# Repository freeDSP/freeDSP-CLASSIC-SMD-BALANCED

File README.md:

# freeDSP-CLASSIC-SMD-BALANCED 
SMD Version with 1 I2S expansion header and balanced inputs/outputs and freeUSBi onboard.

## Upgrades from CLASSIC SMD A
- balanced audio inputs and outputs
- supports balanced interconnections with +6dBu (ARD nominal signal level)
- supports unbalanced interconnections with -10dBV (consumer audio nominal signal level)
- OpAmps supplied with +5V
- DC power input on barrel jack
- 1 standard I2S expansion header

For more information, please refer to the website [freedsp.github.io](https://freedsp.github.io/) and the documentation.  

## Status
Ready

## License

This work and all other materials under https://github.com/freeDSP are licensed under a <a rel="license" href="http://creativecommons.org/licenses/by-sa/4.0/legalcode">Creative Commons Attribution Share-Alike 4.0 license</a>. This allows for both personal and commercial derivative works, as long as they credit freeDSP and release their designs under the same license.

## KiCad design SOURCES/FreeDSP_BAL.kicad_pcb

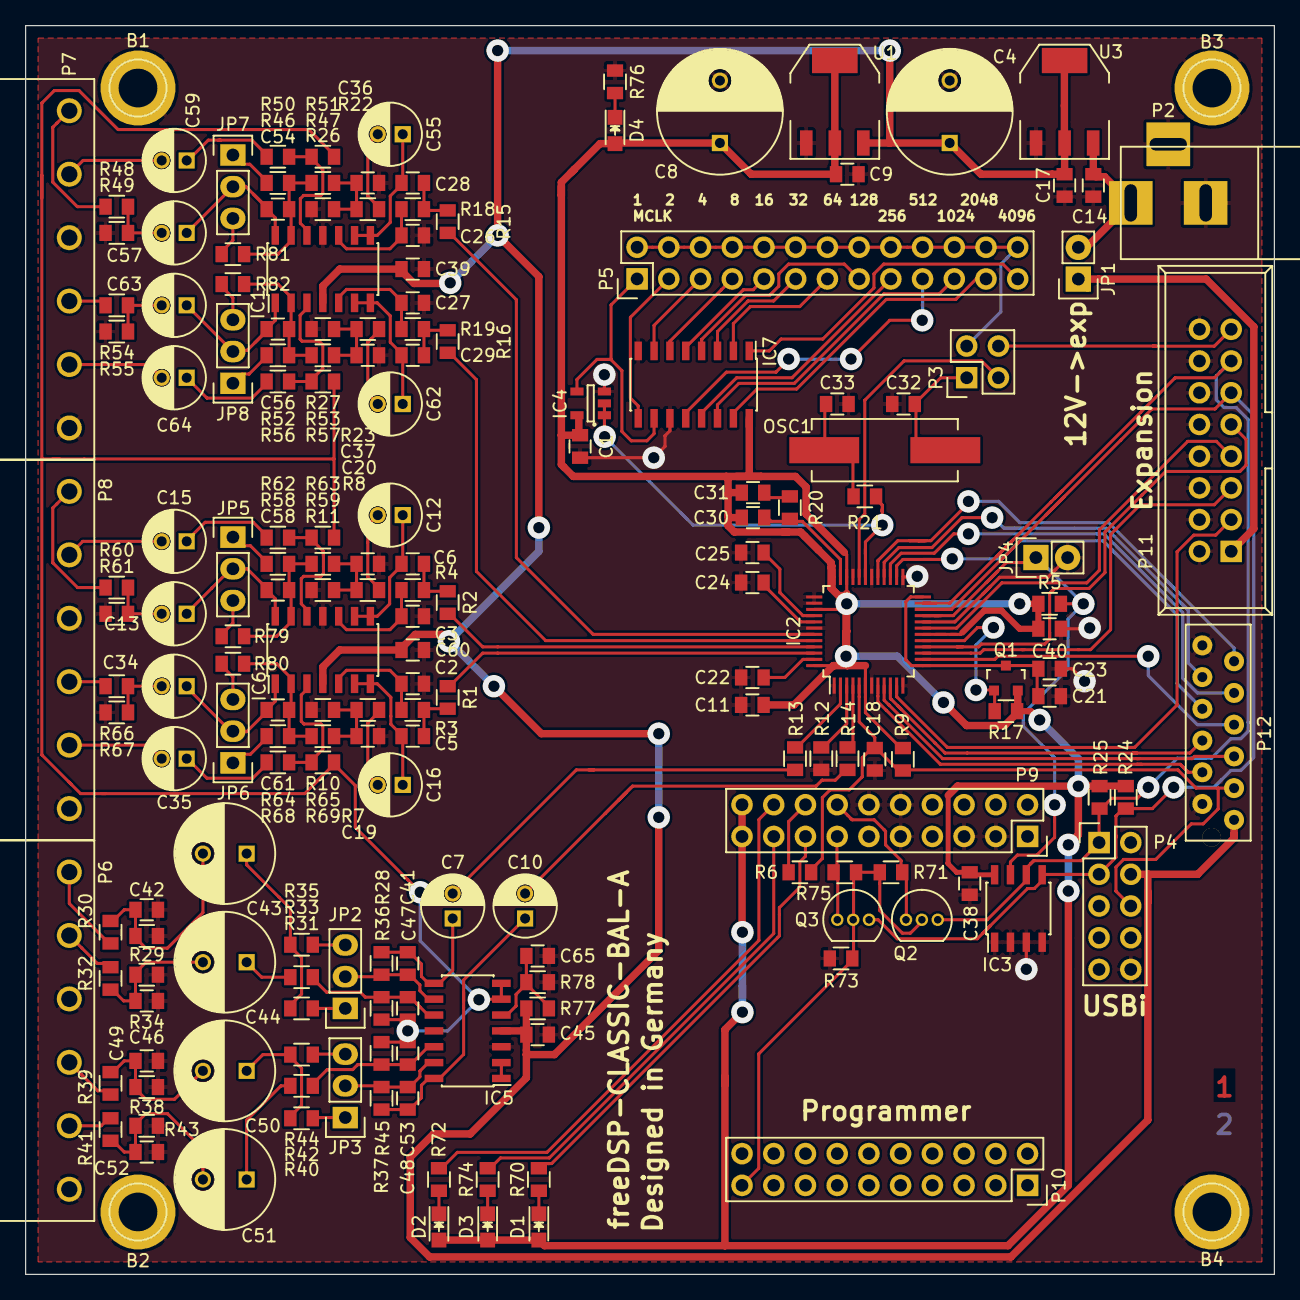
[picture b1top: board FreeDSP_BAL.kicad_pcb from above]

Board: 2 copper layers, 100.0 x 100.0 mm, 187 parts (0 on the bottom side), 148 nets.

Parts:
B1, B2, B3, B4: TEST_1P; 1pin
C1, C17, C23, C38, C39, C40, C45, C60, C65: 100n; C0805-X7R
C2, C3, C26, C27: 150p; C0805-X7R
C4, C8: 220u./35V; C_Radial_D10_L13_P5
C5, C6, C28, C29: 470p; C0805-X7R
C7, C10, C12, C13, C15, C16, C34, C35, C55, C57, C59, C62, C63, C64: 47u0./16V; C_Radial_D5_L11_P2
C9, C11, C14, C21, C22, C24, C25: 10u0; C0805-X7R
C18: 10n0; C0805-X7R
C19, C20, C30, C36, C37: 3n30; C0805-X7R
C31: 56n0; C0805-X7R
C32, C33: 22p0; C0805-X7R
C41, C47, C48, C53: 27p0; C0805-X7R
C42, C46, C49, C52: 100p; C0805-X7R
C43, C44, C50, C51: 47u0./35V; C_Radial_D8_L11.5_P3.5
C54, C56, C58, C61: 47p0; C0805-X7R
D1, D4: GREEN; LED_0805
D2, D3: RED; LED_0805
IC1, IC5, IC6: AD8608ARZ; SOIC-14_3.9x8.7mm_Pitch1.27mm
IC2: ADAU1701; LQFP-48_7x7mm_Pitch0.5mm
IC3: 24AA256; SOIC-8_3.9x4.9mm_Pitch1.27mm
IC4: SN74LVC1G08DBVR; SOT-23-5
IC7: 74HC4040D; SOIC-16_3.9x9.9mm_Pitch1.27mm
JP1, JP4: JUMPER; Pin_Header_Straight_1x02
JP2, JP3, JP5, JP6, JP7, JP8: JUMPER3; Pin_Header_Straight_1x03
OSC1: 24M576Hz; Crystal_HC49-SD_SMD
P2: BARREL_JACK
P3: CONN_02X02; Pin_Header_Straight_2x02
P4: USBi; Pin_Header_Straight_2x05
P5: CONN_02X13; Pin_Header_Straight_2x13
P6, P7, P8: CONN_01X06; SL_5.08HC-06-90
P9, P10: CONN_02X10; Socket_Strip_Straight_2x10
P11: MM-16G; IDC_Header_Straight_16pins
P12: MM-12G
Q1: ZXTP25040DFHTA; SOT-23
Q2, Q3: 2N7000; TO-92_Inline_Narrow_Oval
R1, R2, R3, R4, R15, R16, R18, R19: 4K75; C0805-RES
R5, R24, R25, R28, R36, R37, R45, R47, R53, R59, R65, R71, R75: 10K0; C0805-RES
R6, R20, R70, R72, R74, R76: 470R; C0805-RES
R7, R8, R22, R23: 6K04; C0805-RES
R9, R12: 18K0; C0805-RES
R10, R11, R26, R27: 49K9; C0805-RES
R13, R14: 7K15; C0805-RES
R17: 1K00; C0805-RES
R21, R30, R32, R39, R41: 100R; C0805-RES
R29, R34, R38, R43: 100K; C0805-RES
R31, R33, R40, R42, R79, R80, R81, R82: 17K4; C0805-RES
R35, R44, R46, R52, R58, R64: 3K57; C0805-RES
R48, R54, R60, R66: 56R0; C0805-RES
R49, R55, R61, R67: 22K0; C0805-RES
R50, R51, R56, R57, R62, R63, R68, R69: 27R0; C0805-RES
R73: 1M00; C0805-RES
R77, R78: 47K0; C0805-RES
U1: 78033; SOT-223_Reg_MAE
U3: 7805; SOT-223_Reg_MAE

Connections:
3V3: C1.1, C8.1, C9.1, C11.1, C30.1, C31.1, C38.1, C40.1, D1.2, D2.2, D3.2, D4.2, IC2.6, IC2.18, IC2.34, IC2.36, IC2.39, IC2.48, IC3.8, IC4.5, IC7.16, P9.19, P9.20, Q1.2, R5.2, R9.2, R17.2, R24.2, R25.2, U1.VO
+5V: C4.1, C17.1, C39.2, C45.2, C60.2, IC1.4, IC5.4, IC6.4, P4.4, P12.1, R77.1, U1.VI, U3.VO
/DAC0: IC2.43, R15.2
/DAC1: IC2.44, R16.2
/DAC2: IC2.45, R2.2
/DAC3: IC2.46, R1.2
/IN1: IC2.2, R13.2
/IN1+: P6.1, R30.2
/IN1-: P6.2, R32.2
/IN2: IC2.4, R14.2
/IN2+: P6.4, R39.2
/IN2-: P6.5, R41.2
/OUT1: C36.1, R22.2, R26.1, R47.2
/OUT1+: P7.1, R48.1
/OUT1-: C59.2, P7.2
/OUT2: C37.1, R23.2, R27.1, R53.2
/OUT2+: P7.4, R54.1
/OUT2-: C64.2, P7.5
/OUT3: C20.1, R8.2, R11.1, R59.2
/OUT3+: P8.1, R60.1
/OUT3-: C15.2, P8.2
/OUT4: C19.1, R7.2, R10.1, R65.2
/OUT4+: P8.4, R66.1
/OUT4-: C35.2, P8.5
/USB_LED1: P9.15, R70.2
/USB_LED2: P9.18, R72.2
/USB_LED3: P9.17, R74.2
/USB_PWR_ON: P10.19, Q2.2, Q3.2, R71.2, R73.2, R75.1
/USB_SCL: P9.14, Q2.1, R71.1
/USB_SDA: P9.13, Q3.1, R75.2
/Vcom: C47.2, C53.2, IC5.6, IC5.7, R36.2, R45.2, R51.2, R57.2, R63.1, R69.2
/WP: IC2.21, IC3.7, JP4.1, R5.1
BCLK: IC2.19, P11.7
GND: B1.1, B2.1, B3.1, B4.1, C1.2, C2.1, C3.1, C4.2, C8.2, C9.2, C11.2, C14.2, C17.2, C18.2, C19.2, C20.2, C21.2, C22.2, C23.2, C24.2, C25.2, C26.1, C27.1, C32.2, C33.2, C36.2, C37.2, C38.2, C39.1, C40.2, C42.1, C45.1, C46.1, C49.1, C52.1, C60.1, C65.1, IC1.11, IC2.1, IC2.7, IC2.12, IC2.20, IC2.25, IC2.30, IC2.33, IC2.37, IC2.38, IC2.42, IC3.1, IC3.2, IC3.3, IC3.4, IC4.3, IC5.3, IC5.11, IC6.11, IC7.8, IC7.11, JP4.2, P2.2, P2.3, P4.10, P6.3, P6.6, P7.3, P7.6, P8.3, P8.6, P9.3, P9.5, P9.9, P9.10, P9.12, P11.2, P11.4, P11.6, P11.8, P11.10, P11.12, P11.14, P11.16, P12.2, P12.12, R10.2, R11.2, R12.1, R26.2, R27.2, R29.1, R34.1, R38.1, R43.1, R49.2, R55.2, R61.2, R67.2, R73.1, R76.2, R78.2, U1.GND, U3.GND
LRCLK: IC2.16, P11.9
MCLK: P3.4, P11.15
MDI: IC2.11, P11.3
MDO: IC2.15, P11.5
MP1: IC2.10, P12.6
MP2: IC2.29, P12.11
MP3: IC2.28, P12.10
MP4: IC2.8, P12.4
MP5: IC2.9, P12.5
MP7: IC2.14, P12.7
MP8: IC2.27, P12.9
MP9: IC2.26, P12.8
unnamed: C2.2, IC6.5, R3.1
unnamed: C3.2, IC6.10, R4.1
unnamed: C5.2, R1.1, R3.2
unnamed: C6.2, R2.1, R4.2
unnamed: C7.2, R13.1
unnamed: C10.1, C48.1, IC5.14, R37.1
unnamed: C10.2, R14.1
unnamed: C6.1, C12.1, IC6.8, IC6.9
unnamed: C12.2, R8.1
unnamed: C13.1, C58.1, IC6.14, JP5.2
unnamed: C13.2, R60.2, R61.1
unnamed: C15.1, R62.1
unnamed: C5.1, C16.1, IC6.6, IC6.7
unnamed: C16.2, R7.1
unnamed: C21.1, C23.1, IC2.13, IC2.24, Q1.3
unnamed: C22.1, IC2.47
unnamed: C24.1, IC2.41
unnamed: C25.1, IC2.40
unnamed: C26.2, IC1.10, R18.1
unnamed: C27.2, IC1.5, R19.1
unnamed: C28.1, C55.1, IC1.8, IC1.9
unnamed: C28.2, R15.1, R18.2
unnamed: C29.1, C62.1, IC1.6, IC1.7
unnamed: C29.2, R16.1, R19.2
unnamed: C30.2, IC2.35, R20.2
unnamed: C31.2, R20.1
unnamed: C32.1, OSC1.2, P3.1
unnamed: C33.1, OSC1.1, R21.2
unnamed: C34.1, C61.1, IC6.1, JP6.2
unnamed: C34.2, R66.2, R67.1
unnamed: C35.1, R68.1
unnamed: C7.1, C41.1, IC5.8, R28.1
unnamed: C41.2, IC5.9, JP2.2, R28.2
unnamed: C42.2, C43.2, R29.2, R30.1
unnamed: C43.1, R31.2, R35.2
unnamed: C44.1, R33.2
unnamed: C44.2, C46.2, R32.1, R34.2
unnamed: C47.1, IC5.10, R33.1, R36.1
unnamed: C48.2, IC5.13, JP3.2, R37.2
unnamed: C49.2, C50.2, R38.2, R39.1
unnamed: C50.1, R40.2, R44.2
unnamed: C51.1, R42.2
unnamed: C51.2, C52.2, R41.1, R43.2
unnamed: C53.1, IC5.12, R42.1, R45.1
unnamed: C54.1, C57.1, IC1.14, JP7.2
unnamed: C54.2, IC1.13, R46.2, R47.1, R81.2
unnamed: C55.2, R22.1
unnamed: C56.1, C63.1, IC1.1, JP8.2
unnamed: C56.2, IC1.2, R52.2, R53.1, R82.2
unnamed: C57.2, R48.2, R49.1
unnamed: C58.2, IC6.13, R58.2, R59.1, R79.2
unnamed: C59.1, R50.1
unnamed: C61.2, IC6.2, R64.2, R65.1, R80.2
unnamed: C62.2, R23.1
unnamed: C63.2, R54.2, R55.1
unnamed: C64.1, R56.1
unnamed: C65.2, IC5.5, R77.2, R78.1
unnamed: D1.1, R70.1
unnamed: D2.1, R72.1
unnamed: D3.1, R74.1
unnamed: D4.1, R76.1
unnamed: IC1.3, R56.2, R57.1
unnamed: IC1.12, R50.2, R51.1
unnamed: IC2.3, R12.2
unnamed: IC2.17, Q1.1, R17.1
unnamed: IC2.31, IC4.1, IC4.2, R21.1
unnamed: IC2.32, P3.3
unnamed: IC4.4, IC7.10, P5.1
unnamed: IC5.1, IC5.2
unnamed: IC6.3, R68.2, R69.1
unnamed: IC6.12, R62.2, R63.2
unnamed: IC7.1, P5.25
unnamed: IC7.2, P5.13
unnamed: IC7.3, P5.11
unnamed: IC7.4, P5.15
unnamed: IC7.5, P5.9
unnamed: IC7.6, P5.7
unnamed: IC7.7, P5.5
unnamed: IC7.9, P5.3
unnamed: IC7.12, P5.19
unnamed: IC7.13, P5.17
unnamed: IC7.14, P5.21
unnamed: IC7.15, P5.23
unnamed: JP1.1, P11.1
unnamed: JP2.1, R31.1
unnamed: JP2.3, R35.1
unnamed: JP3.1, R40.1
unnamed: JP3.3, R44.1
unnamed: JP5.1, R58.1
unnamed: JP5.3, R79.1
unnamed: JP6.1, R64.1
unnamed: JP6.3, R80.1
unnamed: JP7.1, R46.1
unnamed: JP7.3, R81.1
unnamed: JP8.1, R52.1
unnamed: JP8.3, R82.1
unnamed: P3.2, P5.2, P5.4, P5.6, P5.8, P5.10, P5.12, P5.14, P5.16, P5.18, P5.20, P5.22, P5.24, P5.26
unnamed: P9.16, R6.1
SCL: IC2.23, IC3.6, P4.1, P11.13, Q2.3, R25.1
SDA: IC2.22, IC3.5, P4.3, P11.11, Q3.3, R24.1
VCC: C14.1, JP1.2, P2.1, U3.VI
_RESET: C18.1, IC2.5, P4.6, P12.3, R6.2, R9.1

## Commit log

2016-05-02 Init
2016-05-08 Picture of prototype.
2016-05-12 Cleaned BOM (footprints).
2016-05-17 - Added 10K PullUp and GND-Jumper on WP-line - Fixed footprint of Q1
2016-05-19 - Bugfix ADC-Stage: Applied VCC/2 - Changed VCC of OpAmps to +5V - Changed gains, Pro: +6dBu (ARD-Norm) and Con: -10dBv for full scale
2016-05-20 Bugfix DAC-Stage: Applied VCC/2 - Supplied OpAmps with +5V - Reworked gain settings: Pro +6dBu, Consumer -10dBV
2016-05-21 Changed DC supply connector to barrel jack
2016-05-23 Moved EZ-USB sockets => EZ-USB now fits into standard enclosure.
2016-05-24 Changed expansion header to new standard i2s expansion header
2016-05-24 WB on GND
2016-05-29 Updated Gerber and BOM
2016-05-31 Minor updates
2016-05-31 Added 3D rendering of beta-Ready version.
2016-07-14 Correction of some typos
2016-07-14 Chaged OSC1 to 24.576MHz
2016-08-30 Changed voltage divider for outputs to avoid clipping for full scale (ADAU1701 on prototype gives 2.8Vpp instead of 2.5Vpp)
2016-08-30 Changed expansion header to 2.54 IDC
2016-08-30 Updated Gerbers
2016-09-06 Revision C: Improvement of input and output stages. Added some fault protection.
2026-01-05 Changed website url since the old one is not up anymore
    Updated README to change website URL.
    The old URL pointed to a phishing website.
